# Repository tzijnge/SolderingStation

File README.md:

# SolderingStation

[WIO Terminal](https://wiki.seeedstudio.com/Wio_Terminal_Intro/) adaptation of the [Elektor Platino soldering station](https://www.elektormagazine.com/magazine/elektor-201507/27978)

## Development environment

### Tooling

- [Visual Studio Code](https://code.visualstudio.com/)
- [PlatformIO IDE extension](https://platformio.org/install/ide?install=vscode) for VS Code (recommended in `.vscode/extensions.json`)
  - Installs its own toolchain (GCC ARM, `pio` CLI, etc.) on first use — no separate Arduino IDE or ARM toolchain install needed
- [Teleplot](https://teleplot.fr/) VS Code extension (optional) — for live-plotting the telemetry, see [Telemetry / PID tuning](#telemetry--pid-tuning) below
- Python 3.10 or newer with `pip install -r tools/requirements.txt` (optional) — for the PC tools: remote control with `lrpcc` and the telemetry script, see [Remote control (LotusRPC)](#remote-control-lotusrpc) below
- [KiCad 10](https://www.kicad.org/) — for the front panel PCB, see [Front panel](#front-panel) below

### Hardware target

- [Seeed WIO Terminal](https://wiki.seeedstudio.com/Wio_Terminal_Intro/) (SAMD51, Cortex-M4F)
- `atmelsam` platform, `board = seeed_wio_terminal`, `framework = arduino` (see `platformio.ini`)

### Libraries

Declared in `platformio.ini` under `lib_deps`, fetched automatically by PlatformIO on build:

- [LovyanGFX](https://github.com/lovyan03/LovyanGFX) — drives the 2.4" ILI9341 LCD (`#include <LovyanGFX.hpp>`, class `LGFX`), using genuine DMA-based SPI for speed. Needs `-D LGFX_AUTODETECT -D LGFX_WIO_TERMINAL` in `platformio.ini`'s `build_flags`, since PlatformIO's `seeed_wio_terminal` board definition doesn't define `ARDUINO_WIO_TERMINAL`, which LovyanGFX's autodetect normally keys off.
- [SparkFun_Qwiic_Twist_Arduino_Library](https://github.com/sparkfun/SparkFun_Qwiic_Twist_Arduino_Library) — driver for the Qwiic Twist rotary encoder, connected via a Grove-to-Qwiic cable on the WIO Terminal's Grove I2C port
- [ETL (Embedded Template Library)](https://github.com/ETLCPP/etl) — used throughout for containers/utilities in this interrupt-driven design
- [Arduino-PID-Library](https://github.com/br3ttb/Arduino-PID-Library) — drives the tip-temperature PID control loop
- [LotusRPC](https://github.com/tzijnge/LotusRpc) — remote control and telemetry over USB. Not a `lib_deps` entry: its server code is generated during the build, see [Remote control (LotusRPC)](#remote-control-lotusrpc) below

### Building and uploading

Build and upload using the PlatformIO sidebar in VS Code (project/build/upload icons in the PlatformIO toolbar), or the equivalent `pio run` / `pio run -t upload` commands from a PlatformIO Core CLI.

### Known build gotchas

- `Arduino.h` (with the WIO Terminal's `variant.h` it pulls in) `#define`s names that break standard library and ETL headers parsed after it: the function-like macros `min`, `max`, `abs` and `round`, and pin names such as `D1` and `D2`, which ETL uses as template parameter names. The fix is to include the affected headers *before* `Arduino.h`: their include guards then keep them from being parsed again once the macros exist. That's the include block at the very top of `src/main.cpp`. If a newly used `<...>` or `etl/...` header fails with odd errors pointing into `Arduino.h` or `variant.h`, add it to that block. `main.cpp` is the only source file; a second `.cpp` file would need the same block, or a forced include (`-include`) in `platformio.ini`.
- LovyanGFX's rotation numbering for this board is offset by 180° from the old TFT_eSPI-based fork this project used to use — call `tft.setRotation(1)` (not `3`) for correct upright landscape orientation.

### Images

Images on the display, such as the warning sign on the fault screen, are drawn as SVG files in `assets/`. A script converts each one into a C++ header in `src/images/`, which the firmware draws by calling the header's `draw()` function. The generated headers are committed, so building the firmware doesn't need Python.

| SVG | Generated header | Used in |
|---|---|---|
| `assets/warning_sign.svg` | `src/images/WarningSign.h` | `src/safety/FaultScreen.h` |

To change an image:

1. Edit the SVG, in a text editor or a drawing program such as Inkscape. Draw at the size it should appear on screen: one SVG unit is one pixel. The display has 320 × 240 pixels.
2. Install the script's dependencies (only needed once):

   ```
   pip install -r tools/requirements.txt
   ```

3. Regenerate the header. The last argument is the C++ namespace the image gets:

   ```
   python tools/svg_to_bitmap.py assets/warning_sign.svg src/images/WarningSign.h WarningSign
   ```

   The script prints the image's size in bytes and how much the colour reduction (see below) changed it.
4. Build and upload as usual, and commit both the SVG and the regenerated header.

Things to know:

- Never edit the generated header by hand; the next regeneration overwrites it.
- To save flash, images are stored with a limited colour table (a palette): by default 16 colours, so each pixel takes 4 bits instead of the 16 bits of full colour. The warning sign takes about 4.9 KB instead of 19.5 KB. 16 colours is plenty for icons made of a few flat colours plus the smoothed shades along their edges. If the script reports many changed pixels for a more colourful image, use `--bits 8` (256 colours, 8 bits per pixel). For an image with only 2 or 4 flat colours and no smoothing, `--bits 1` or `--bits 2` makes it smaller still.
- The script renders the image on a black background, the screen background, so its smoothed edges blend into black. Transparent parts of the SVG come out black.
- The header contains the image's `WIDTH`, `HEIGHT` and a `draw(tft, x, y)` function, which draws it with its top-left corner at (x, y). All its data is stored in flash, not RAM.
- If the image size changes, check the layout of the screen that uses it. `FaultScreen.h` centres the warning sign horizontally, but its vertical position (`SIGN_Y`) and the positions of the text above and the temperature below are fixed.
- To add a new image, run the script with a new SVG, header name and namespace, add a row to the table above, and include the header where the image is drawn.

## Hardware

### Inputs

- Three onboard buttons (`WIO_KEY_A`/`B`/`C`, pins 28/29/30). Physical left-to-right position does **not** match alphabetical pin naming — confirmed on-device: left = `WIO_KEY_C`, middle = `WIO_KEY_B`, right = `WIO_KEY_A`.
- [SparkFun Qwiic Twist](https://www.sparkfun.com/products/15083) rotary encoder, connected via Grove-to-Qwiic cable into the WIO Terminal's Grove I2C port (standard `Wire`, no special Qwiic-specific setup needed). Its INT pad is wired to `BCM21` (40-pin header physical position 40) — confirmed working. **Do not** wire it to `BCM2` (physical position 3): despite the Arduino pin table labeling it as a free, independent I2C bus, it shares a net at the PCB level with the Grove I2C bus and breaks the Twist's communication when wired, even before any new firmware is uploaded.
  - The Twist library never enables its own interrupt register (`TWIST_ENABLE_INTS`, `0x04`) — `setup()` writes it directly over raw I2C (`0x03`, encoder + button interrupt bits) to get the INT line to assert at all.
  - `twist.setIntTimeout(0)` is set to avoid the default ~250ms coalescing delay on rotation events, for a responsive display.

### Tip temperature sensing

Signal chain from the soldering tip's thermocouple to the ADC reading (see `TipTemperature.h`):

```
tip sensor (16uV/°C) -> PCB amplifier (gain 68000/150) -> ADC (12-bit, 3.3V ref, pin A3/BCM24/40-pin header pin 18)
```

### Heater and power supply

- The soldering iron's heating element measures ~2Ω and is rated 40W (implied design voltage ≈ 9–12V, not the 19V a laptop supply would suggest).
- Power supply: **12V, 5A** (not the originally-considered 19V/3A laptop brick, which was bench-tested and found both underpowered — couldn't supply the ~9.5A peak current the element draws at 19V without significant ripple — and would have driven the element to ~4.5x its rated power at full duty).
- The reverse-polarity protection diode on the supply input is a **Schottky** diode (not silicon) — its lower forward voltage drop (~0.2–0.3V vs. ~0.7V) leaves more of the supply's voltage headroom for the heater.
- PWM output pin: `BCM23`/A2.

⚠️ **Safety note:** the firmware cuts the heater when the tip goes above a fixed temperature limit (`OVER_TEMPERATURE_LIMIT_C` in `src/safety/SafetyMonitor.h`). The fault stays latched, shown on a separate fault screen, until the tip has cooled below the limit and the knob is pressed. It also faults when the heater runs at (near) full power without the tip heating up below 150C (`ThermalRunaway`, catches a shorted sensor within ~3s), or for 15s without a break at any temperature (`HeaterSaturated`). Every fault beeps twice. At the time of writing the firmware still has:

- no sensor fault detection: a sensor that fails while the tip is hot is only caught by the 15s saturation check;
- no power or duty cap;
- no hardware watchdog.

These are tracked in issues #3, #4 and #7. Until they're implemented, do not leave the station heating unattended.

### Front panel

A PCB used as the enclosure's front panel (black soldermask, white silkscreen), KiCad 10 project in `hardware/frontpanel/`. It carries the mains switch, the WIO Terminal (plugged into a 40-pin header on the front), the Qwiic Twist knob (on the back, plugged into a socket) and the XLR socket for the iron. All routing is on the back layer, so nothing shows through the soldermask on the front.

The board is generated by `generate_frontpanel.py`. To adapt it to your own enclosure and parts, edit the constants at the top of the script and run it with the Python interpreter that comes with KiCad 10:

```
<KiCad install dir>/bin/python generate_frontpanel.py
```

The main parameters (all in mm, from the top-left corner as seen from the front):

- `PANEL_W`, `PANEL_H`, `PANEL_THICKNESS`, `SLOT_DEPTH` — panel size and how far it sits in the enclosure's slots.
- `SWITCH_X`, `WIO_X`, `KNOB_X`, `XLR_X` — horizontal position of each part; everything is centred vertically. The connectors, tracks and silkscreen follow.
- `SWITCH_HOLE_D`, `ENCODER_HOLE_D`, `XLR_HOLE_D`, `XLR_SCREW_DX` — cutouts for your particular parts.
- `BACK_CONN_POS`, `BACK_CONN_EXIT` — where the connector to the iron PCB sits and which way its cable leaves.
- `CREDITS`, `REPO_URL` — text and QR code on the back.

After regenerating, open the board in KiCad and run DRC. The script overwrites `frontpanel.kicad_pcb`, so either keep making changes in the script, or edit in KiCad and stop using the script.

The connector to the soldering iron PCB (J3, 4-pin JST-PH) — the iron PCB must use the same order:

| Pin | Signal | WIO |
|---|---|---|
| 1 | TEMP (tip temperature, ADC) | `A3`/`BCM24` |
| 2 | GND | |
| 3 | HEATER PWM | `BCM23` |
| 4 | 5V (powers the WIO) | |

A second 4-pin JST-PH (J4) brings out three spare GPIOs (`BCM7`, `BCM12`, `BCM16`) and GND for debugging.

Things to watch out for:

- The WIO's 40-pin header follows the Raspberry Pi pinout exactly. The pin table in the board's `variant.h` wrongly shows pin 17 as GND; it's 3.3V.
- The Twist's encoder is on its bottom side, so seen from the front its pin row is mirrored relative to SparkFun's drawings.
- The copper pours stay clear of the board edge and of the XLR and mains switch, so logic GND can't touch the earthed enclosure, the XLR chassis or mains.
- The panel must fill the enclosure's slots (2.2 mm here). A 2.0 mm board costs about four times as much as a 1.0 or 1.6 mm one, so here two identical 1.0 mm boards are stacked (`PANEL_THICKNESS` = 1.0): the back one carries the parts, the front one only shows its front side, and the parts' screws clamp them together. The 40-pin header then goes through both boards — use one with pins long enough to solder on the back of the back board.
- Have the fab leave its order number off the board (at JLCPCB: "Mark on PCB: Remove Mark", same price).

## Remote control (LotusRPC)

The station is a [LotusRPC](https://github.com/tzijnge/LotusRpc) server on its USB serial port. PC tools can simulate the knob and buttons, read the station's state, and receive the telemetry. The interface is defined in `rpc/soldering_station.lrpc.yaml`:

| Service | Functions and streams |
|---|---|
| `input` | `press`, `rotate <steps>`, `button left\|middle\|right` — the same events as the real knob and buttons, so they go through the same limits and fault handling. Like the knob, a press also acknowledges a fault and can switch the heater on. |
| `status` | `state`, `fault`, `setpoint`, `tip_temperature` (measured and filtered), `duty`, and `all` for all of these in one call |
| `telemetry` | stream `samples`: one sample every 100 ms while started (see below) |

**Code generation.** The server code is generated during every PlatformIO build by `tools/lrpc_generate.py` (`extra_scripts` in `platformio.ini`), into the build directory; nothing generated is committed. The script installs the LotusRPC version pinned in `tools/requirements.txt` in a venv of its own (`.pio/lrpc-venv`, not PlatformIO's own Python, whose packages LotusRPC's pins could conflict with), and only regenerates when the definition or the pin changed. The generated `soldering_station.hpp` is included in the block before `Arduino.h` in `main.cpp` (see [Known build gotchas](#known-build-gotchas)).

**lrpcc.** `lrpcc` is LotusRPC's command-line client. It reads `lrpcc.config.yaml`, which is machine-specific and therefore git-ignored. Create it in the repo root, with the station's serial port:

```yaml
definition_url: rpc/soldering_station.lrpc.yaml
transport_type: serial
transport_params:
  port: COM5
  timeout: 2
```

Run `lrpcc` from the repo root (it resolves `definition_url` against the working directory):

```
lrpcc input press
lrpcc input rotate 5
lrpcc input rotate -- -5
lrpcc input button left
lrpcc status state
lrpcc status tip_temperature
lrpcc status all
```

The serial port can only be open in one program at a time: `lrpcc` can't be used while the telemetry script runs.

## Telemetry / PID tuning

`tools/telemetry.py` starts the `telemetry` service's `samples` stream and forwards each sample to [Teleplot](https://teleplot.fr/) over UDP (port 47269, Teleplot's default) as `name:value` lines. Unlike over serial, there's no `>` in front: over UDP, Teleplot reads that as a log message.

```
python tools/telemetry.py [--port COM5]
```

Without `--port` it takes the port from `lrpcc.config.yaml`. Open Teleplot in VS Code (not connected to the serial port, which the script holds); it plots `setpoint` (0 while not On), `measured`, `measuredFiltered`, `measuredAvg` (2 s moving average, calculated by the script), `duty`, `adcRaw` and `fault`. Ctrl+C stops the stream. The station also stops it when the port is closed, so a killed script leaves nothing running.

`tools/capture.py` reads the same stream for a few seconds (`--seconds`, default 10) and prints a summary instead of plotting: min, max, mean and standard deviation of `adc_raw` and `measured`, the duty, the faults seen and the lowest raw values. With `--csv <file>` it also saves every sample (all telemetry fields) as it arrives, and Ctrl+C ends a capture early and still prints the summary. It's read-only, and meant for characterising the sensor input. It needs the serial port too, so close the telemetry script first.

`TemperatureController`'s `Kp`/`Ki`/`Kd` gains are placeholders — this project has no characterized plant model (heater wattage, thermal mass, sensor lag), so they need on-device tuning: start with pure P, observe steady-state behavior, add `Ki` to remove steady-state error, and only add `Kd` afterward if overshoot still needs taming.

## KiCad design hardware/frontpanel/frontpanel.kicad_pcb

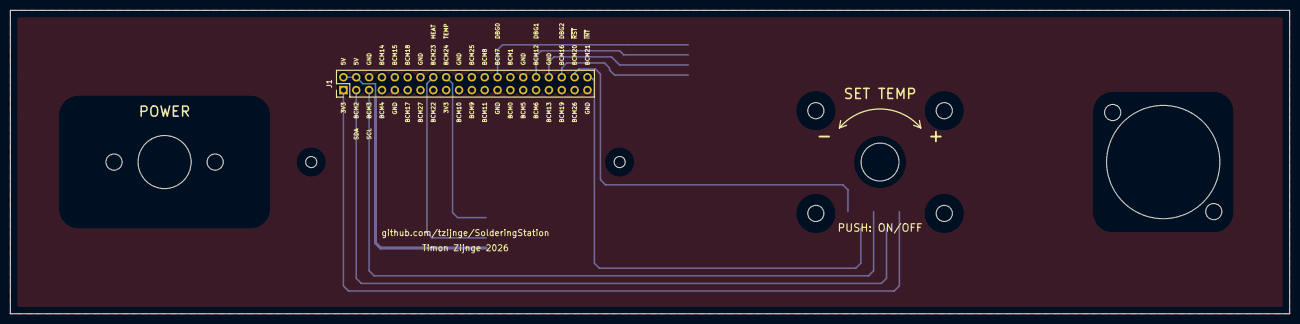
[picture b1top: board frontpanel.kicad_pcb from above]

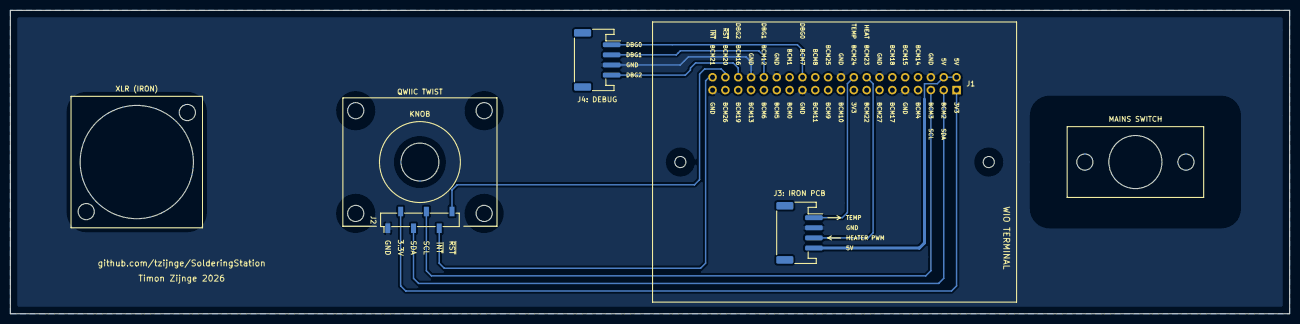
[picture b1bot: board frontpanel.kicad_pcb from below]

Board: 2 copper layers, 253.0 x 60.0 mm, 14 parts (3 on the bottom side), 12 nets.

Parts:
H1, H2: MountingHole_2.2mm_M2
H3, H4, H5, H6, H7, H8, H9, H10: MountingHole_3.2mm_M3
J1: PinHeader_2x20_P2.54mm_Vertical
J2: PinSocket_1x06_P2.54mm_Vertical_SMD_Pin1Left
J3, J4: JST_PH_S4B-PH-SM4-TB_1x04-1MP_P2.00mm_Horizontal

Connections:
+3V3: J1.1, J2.5
+5V: J1.2, J1.4, J3.4
DBG0: J1.26, J4.1
DBG1: J1.32, J4.2
DBG2: J1.36, J4.4
GND: J1.6, J1.9, J1.14, J1.20, J1.25, J1.30, J1.34, J1.39, J2.6, J3.2, J4.3
HEATER_PWM: J1.16, J3.3
I2C_SCL: J1.5, J2.3
I2C_SDA: J1.3, J2.4
TIP_ADC: J1.18, J3.1
TWIST_INT: J1.40, J2.2
TWIST_RST: J1.38, J2.1

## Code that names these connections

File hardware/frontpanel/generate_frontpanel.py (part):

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TWIST_PIN_ROW_DY = 11.43          # pin row below the encoder
# Pin row in SparkFun's top view, left to right (x = 8.89 ... 21.59 mm);
# reversed below to get the order as seen from the front.
_TWIST_PINS_TOP_VIEW = ["GND", "+3V3", "I2C_SDA", "I2C_SCL", "TWIST_INT", "TWIST_RST"]
_TWIST_LABELS_TOP_VIEW = ["GND", "3.3V", "SDA", "SCL", "~{INT}", "~{RST}"]  # silkscreen, ~{} = overbar
TWIST_PINS = _TWIST_PINS_TOP_VIEW[::-1]
TWIST_PIN_LABELS = _TWIST_LABELS_TOP_VIEW[::-1]
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# pin: (net, silkscreen label); GND between the heater PWM and the tip ADC signal.
# Order matches the routing: the tracks arrive from the header, left to right,
# as 5V, HEAT, TEMP, so pin 1 (top) is TEMP and pin 4 (bottom) is 5V.
BACK_CONN_PINS = {1: ("TIP_ADC", "TEMP"), 2: ("GND", "GND"), 3: ("HEATER_PWM", "HEATER PWM"), 4: ("+5V", "5V")}
# Signal direction arrows next to the labels: +1 = out through the cable (to the
# soldering iron PCB), -1 = in from the cable (to the WIO)
BACK_CONN_ARROWS = {"HEATER_PWM": +1, "TIP_ADC": -1}
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DEBUG_CONN_EXIT = (1, 0)
# pin: (net, silkscreen label, WIO header pin). Order matches the routing (no
# crossings): the further left the header pin, the higher the connector pin.
DEBUG_CONN_PINS = {1: ("DBG0", "DBG0", 26), 2: ("DBG1", "DBG1", 32),
                   3: ("GND", "GND", 34), 4: ("DBG2", "DBG2", 36)}
DEBUG_CONN_TITLE = "J4: DEBUG"

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
# To the Twist: 3.3V, SDA and SCL straight down from the header, along the
# bottom under the JST, and up into the socket between its staggered pads
for header_pin, socket_pin, net_name in ((1, 5, "+3V3"), (3, 4, "I2C_SDA"), (5, 3, "I2C_SCL")):
    (hx, hy_), (sx, sy) = pad_at(j1, header_pin), pad_at(j2, socket_pin)
    route(net_name, [(hx, hy_), (hx, BUS_Y[net_name]), (sx, BUS_Y[net_name]), (sx, sy)], SIGNAL_W)
# INT from pin 40 (BCM21): right, down to just above the bus, into the socket from below
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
